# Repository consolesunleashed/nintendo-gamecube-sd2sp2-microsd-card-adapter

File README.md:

# Nintendo GameCube SD2SP2 MicroSD Card Adapter

An aesthetically upgraded version of Citrus3000psi's SD2SP2 v1.2a.

Read more about this project from the creator of the original https://github.com/citrus3000psi/SD2SP2

## Manufacturing

- 1.2mm PCB thickness.
- ENIG finish.

## Version History

- v1.2b - 05/04/2021

## Donate

Working on designs to release for free can be both time consuming and expensive. If you like what I do, a small donation will go a long way in helping me continue to serve the modding community as best as I can, with many more free and original guides, designs, and ideas to come.

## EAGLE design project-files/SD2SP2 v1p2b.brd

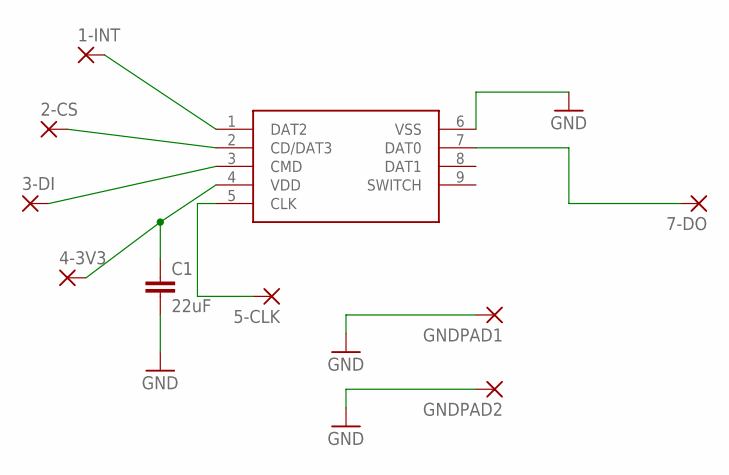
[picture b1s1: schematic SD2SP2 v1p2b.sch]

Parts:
1-INT, 2-CS, 3-DI, 4-3V3, 5-CLK, 7-DO: PADSRECTANGLE-1,5X7; RECTANGLE-1,5X7
C1: 22uF; C1206
GNDPAD1, GNDPAD2: PADSRECTANGLE-1,5X7; RECTANGLE-1,5X7
J1: SD-CARD-CONNECTOR; 105027-0001

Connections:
GND: C1.2, GNDPAD1.1, GNDPAD2.1, J1.6 (VSS)
unnamed: 4-3V3.1, C1.1, J1.4 (VDD)
unnamed: 1-INT.1, J1.1 (DAT2)
unnamed: 2-CS.1, J1.2 (CD/DAT3)
unnamed: 3-DI.1, J1.3 (CMD)
unnamed: 5-CLK.1, J1.5 (CLK)
unnamed: 7-DO.1, J1.7 (DAT0)

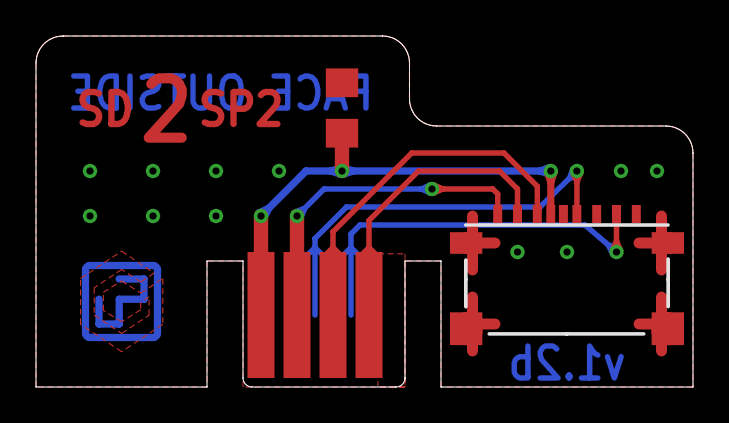
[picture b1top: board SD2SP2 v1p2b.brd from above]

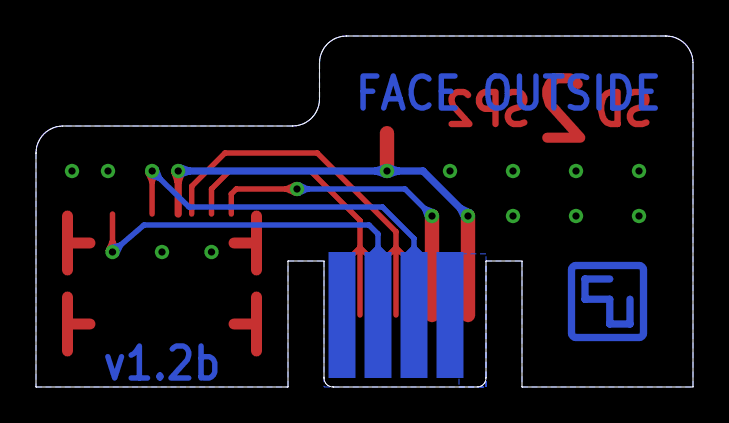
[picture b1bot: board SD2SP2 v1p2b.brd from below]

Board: 2 copper layers, 36.5 x 19.5 mm, 10 parts (4 on the bottom side), 7 nets.
